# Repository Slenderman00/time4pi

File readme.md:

This is how we calibrate the loop.\
Drift = (Actual Time - Expected Time) / Expected Time\
PLL = (5,000,000 kHz × (1 + Drift)) / 32.768 kHz

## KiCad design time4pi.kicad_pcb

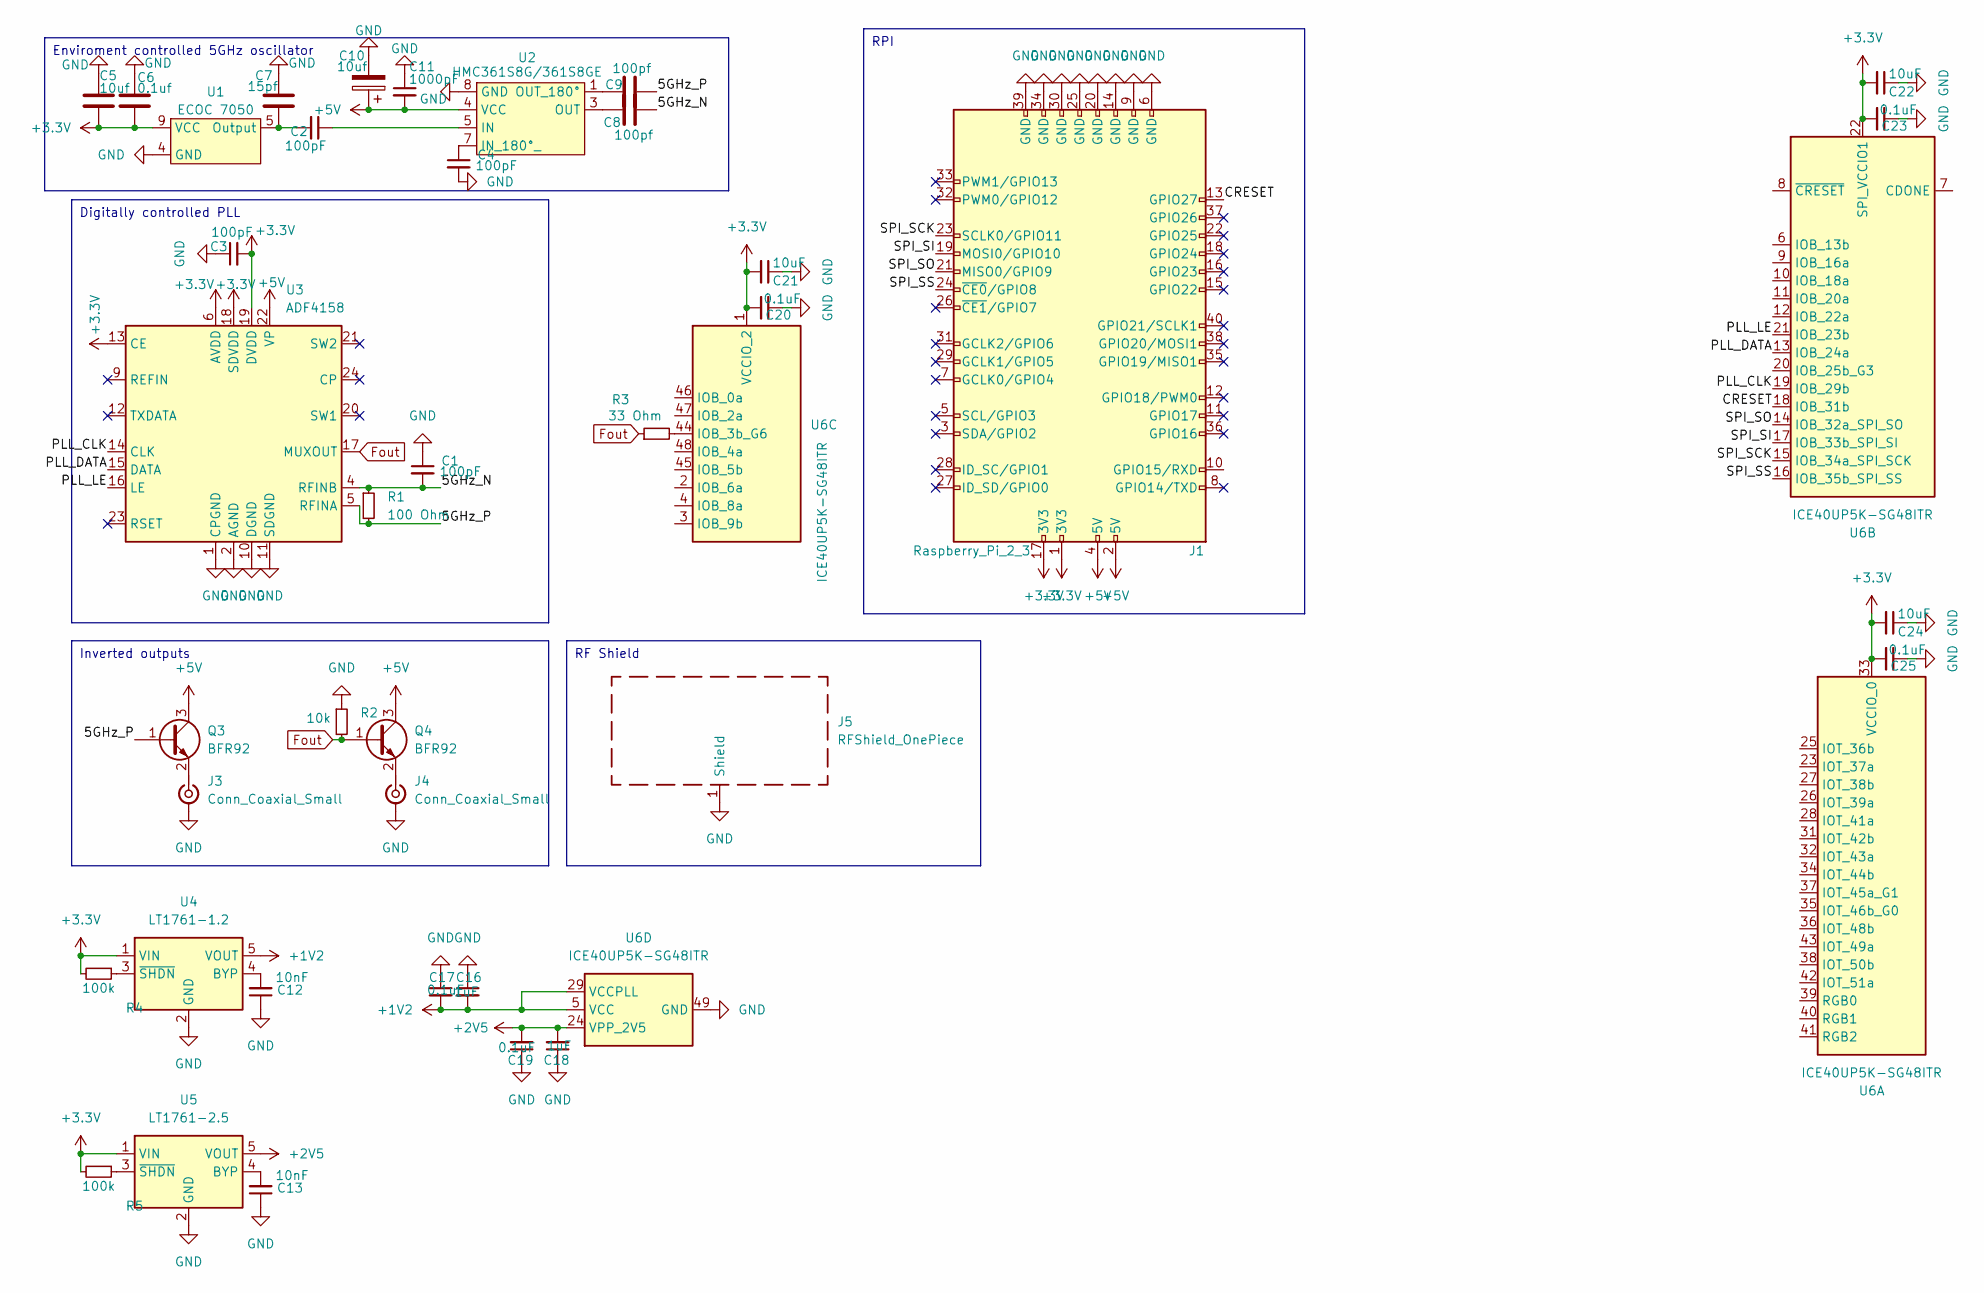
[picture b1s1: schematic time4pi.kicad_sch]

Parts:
C1, C2, C3, C4: 100pF; C_0201_0603Metric
C5: 10uf; C_0201_0603Metric
C6: 0.1uf; C_0201_0603Metric
C7: 15pf; C_0201_0603Metric
C8, C9: 100pf; C_0201_0603Metric
C10: 10uf; CP_EIA-3216-10_Kemet-I
C11: 1000pF; C_0201_0603Metric
C12, C13: 10nF; C_0201_0603Metric
C16, C18: 1uF; C_0201_0603Metric
C17, C19, C20, C23, C25: 0.1uF; C_0201_0603Metric
C21, C22, C24: 10uF; C_0201_0603Metric
J1: Raspberry_Pi_2_3; Raspberry_Pi_Zero_Socketed_THT_FaceDown_MountingHoles
J3, J4: Conn_Coaxial_Small; SMA_Amphenol_901-143_Horizontal
J5: RFShield_OnePiece
Q3, Q4: BFR92; SOT-323_SC-70
R1: 100 Ohm; R_0201_0603Metric
R2: 10k; R_0201_0603Metric
R3: 33 Ohm; R_0201_0603Metric
R4, R5: 100k; R_0201_0603Metric
U1: ECOC 7050
U2: HMC361S8G/361S8GE; HMC361S8G361S8GE
U3: ADF4158; LFCSP-24-1EP_4x4mm_P0.5mm_EP2.5x2.5mm
U4: LT1761-1.2; TSOT-23-5
U5: LT1761-2.5; TSOT-23-5
U6: ICE40UP5K-SG48ITR; QFN-48-1EP_7x7mm_P0.5mm_EP5.6x5.6mm

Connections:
+1V2: C16.2, C17.2, U4.5 (VOUT), U6.5 (VCC), U6.29 (VCCPLL), U6.30 (VCC)
+2V5: C18.2, C19.2, U5.5 (VOUT), U6.24 (VPP_2V5)
+3.3V: C3.2, C5.2, C6.2, C20.2, C21.2, C22.2, C23.2, C24.2, C25.2, J1.1 (3V3), J1.17 (3V3), R4.2, R5.2, U1.9 (VCC), U3.6 (AVDD), U3.7 (AVDD), U3.8 (AVDD), U3.13 (CE), U3.18 (SDVDD), U3.19 (DVDD), U4.1 (VIN), U5.1 (VIN), U6.1 (VCCIO_2), U6.22 (SPI_VCCIO1), U6.33 (VCCIO_0)
+5V: C10.1, C11.2, J1.2 (5V), J1.4 (5V), Q3.3 (C), Q4.3 (C), U2.4 (VCC), U3.22 (VP)
/5GHz_N: C1.2, C8.1, R1.1, U3.4 (RFINB)
/5GHz_P: C9.1, Q3.1 (B), R1.2, U3.5 (RFINA)
/CRESET: J1.13 (GPIO27), U6.18 (IOB_31b)
/PLL_CLK: U3.14 (CLK), U6.19 (IOB_29b)
/PLL_DATA: U3.15 (DATA), U6.13 (IOB_24a)
/PLL_LE: U3.16 (LE), U6.21 (IOB_23b)
/SPI_SCK: J1.23 (SCLK0/GPIO11), U6.15 (IOB_34a_SPI_SCK)
/SPI_SI: J1.19 (MOSI0/GPIO10), U6.17 (IOB_33b_SPI_SI)
/SPI_SO: J1.21 (MISO0/GPIO9), U6.14 (IOB_32a_SPI_SO)
/SPI_SS: J1.24 (~CE0/GPIO8), U6.16 (IOB_35b_SPI_SS)
Fout: Q4.1 (B), R2.2, R3.1, U3.17 (MUXOUT)
GND: C1.1, C3.1, C4.2, C5.1, C6.1, C7.2, C10.2, C11.1, C12.1, C13.1, C16.1, C17.1, C18.1, C19.1, C20.1, C21.1, C22.1, C23.1, C24.1, C25.1, J1.6 (GND), J1.9 (GND), J1.14 (GND), J1.20 (GND), J1.25 (GND), J1.30 (GND), J1.34 (GND), J1.39 (GND), J3.2 (Ext), J4.2 (Ext), J5.1, R2.1, U1.4 (GND), U2.8 (GND), U3.1 (CPGND), U3.2 (AGND), U3.3 (AGND), U3.10 (DGND), U3.11 (SDGND), U3.25 (AGND), U4.2 (GND), U5.2 (GND), U6.49 (GND)
unnamed: J3.1 (In), Q3.2 (E)
unnamed: J4.1 (In), Q4.2 (E)
unnamed: C2.2, C7.1, U1.5 (Output)
unnamed: C2.1, U2.5 (IN)
unnamed: C4.1, U2.7 (IN_180°_)
unnamed: C8.2, U2.3 (OUT)
unnamed: C9.2, U2.1 (OUT_180°)
unnamed: C12.2, U4.4 (BYP)
unnamed: R4.1, U4.3 (~SHDN)
unnamed: C13.2, U5.4 (BYP)
unnamed: R5.1, U5.3 (~SHDN)
unnamed: R3.2, U6.44 (IOB_3b_G6)

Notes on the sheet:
Digitally controlled PLL
RF Shield
Enviroment controlled 5GHz oscillator
Inverted outputs
RPI

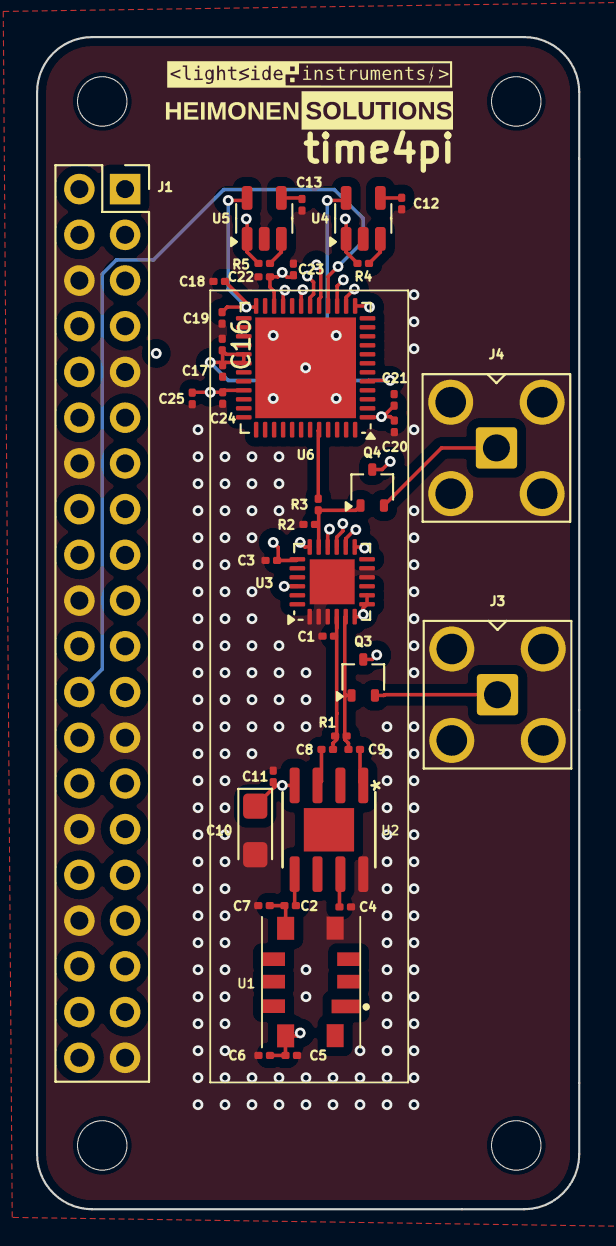
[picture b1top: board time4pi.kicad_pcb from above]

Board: 4 copper layers, 30.1 x 65.1 mm, 39 parts (0 on the bottom side), 28 nets.

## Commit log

2024-11-24 feat: initial release
2024-11-24 fix: symbol values
2024-11-24 feat: finished v0.1
2024-11-24 feat: added logos
2024-11-24 feat: smalled siklscreen text
2024-11-24 feat: more caps
2024-11-24 feat: small changes
2024-11-24 fix: fixed readme
2024-11-24 fix: differential pairs
2024-11-24 fix: internal gnd plane 1
2024-11-25 feat: added ice40fpga
2024-11-25 feat: added stitched vias
2024-11-25 feat: bottom and top layer gnd filled
2024-11-25 fix: moved trace
2024-11-25 fix: smaller silkscreen text
2024-11-25 fix: fpga center pad vias
